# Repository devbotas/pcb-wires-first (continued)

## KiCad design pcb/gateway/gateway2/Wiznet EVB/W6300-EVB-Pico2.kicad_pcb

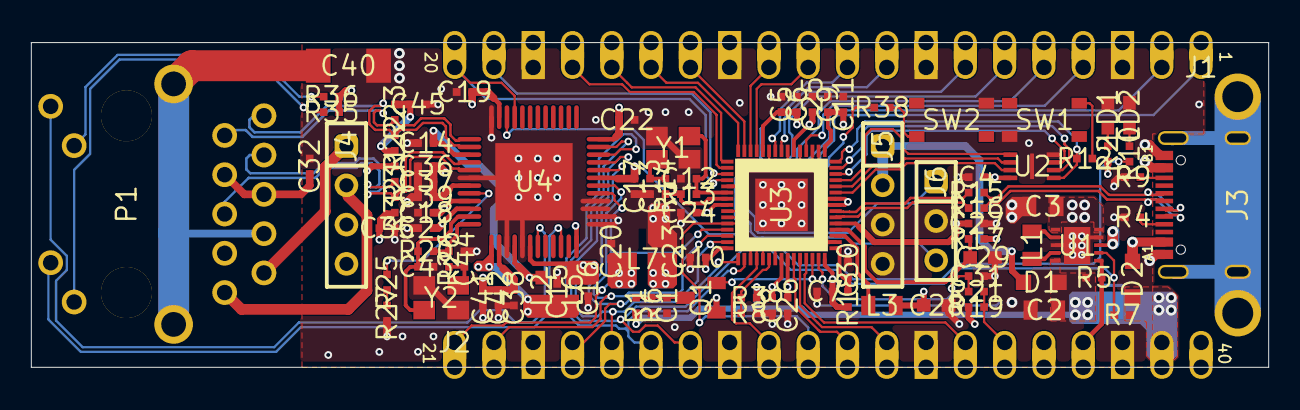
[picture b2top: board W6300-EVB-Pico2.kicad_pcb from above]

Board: 4 copper layers, 80.0 x 21.0 mm, 98 parts (0 on the bottom side), 89 nets.

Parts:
C1, C4, C6, C7, C8, C9, C10, C11, C14, C16, C17, C18, C19, C21, C22, C25, C26, C27, C32, C35, C36, C37, C39, C41, C42, C45: 0.1uF; CAP-0402
C2: 10u; CAP-0805
C3: 47u; CAP-0805
C5, C15, C20, C23, C24, C38: 1uF; CAP-0402
C12, C13: 15pF; CAP-0402
C28, C29: 10uF/1608; CAP-0603
C30, C31: 2u2; CAP-0402
C40: 1nF/2kV; CAP-1808
C43, C44: 18pF; CAP-0402
D1, D2: BAT60A; SOD-323(1-C,2-A)
J1, J2: 2.54mm 1x20 Pin Header DIP; IDC-1X20
J3: *; USB-TYPE-C-31-M-12
J4, J5: Header Socket 1x4_2.54mm; IDC-1X4(SOCKET)
J6: 2.54mm 1x3 Pin Header DIP; IDC-1X3
L1, L3: 2u2; IND-0805
L2, L6, L7: HH-1M1608-121JT; IND-0603
LD1: Green; LED-0603-RED
LD2: Green; LED-0603-GREEN
P1: TRJ4284AHNL; RB1-ZZ-0049
Q1: Q-2N7002; SOT23-3L
R1: 200K; RES-0402
R2, R10: 470R; RES-0402
R3: 5.6K; RES-0402
R4, R9: 5.1k; RES-0402
R5, R6, R7: 100K; RES-0402
R8: 10K; RES-0402
R12, R14, R38: 1K; RES-0402
R13: NC; RES-0402
R15, R16: 27R; RES-0402
R17, R26: 0R; RES-0402
R18: 10R; RES-0402
R19: 200R; RES-0402
R20: 1M; RES-0402
R21: 1R; RES-0402
R22, R23, R31, R32: 49.9R; RES-0402
R25: 12K/1%; RES-0402
R27: 300R; RES-0402
R35, R36: 330R; RES-0402
SW1, SW2: RKB2SJK250SMTR LFS; SW-RKB2
U1: SGM62112-3.3; SGM62112
U2: W25Q16JVUXIQ; SON50P300X200X60-9N
U3: RP2350-A; 7X7)
U4: W6300
Y1: 12MHz; OSC-TZ1067B
Y2: 25MHz; OSC-82J0626

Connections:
1V2A: C14.2, L2.1, U4.3, U4.16
1V2D: C16.2, C17.2, C18.2, C19.2, L6.2, U4.9, U4.18, U4.31, U4.47
1V2O: C15.2, L2.2, L6.1, U4.13
3V3: C3.2, C4.2, C5.2, C6.2, C7.2, C8.2, C9.2, C10.2, C11.2, C20.2, C21.2, C22.2, J2.16, L7.1, Q1.1, R2.1, R17.1, R18.1, R19.1, R35.2, R36.2, U1.1, U1.10, U2.8, U3.1, U3.11, U3.20, U3.30, U3.38, U3.45, U3.53, U3.54, U4.10, U4.24, U4.36
3V3A: C23.2, C32.2, C36.2, C37.2, C38.2, C39.2, C41.2, C42.2, L7.2, P1.R4, P1.R5, U4.7, U4.14
3V3_EN: J2.17, R5.2, U1.6
ACTn: P1.L2, U4.22
ADC_VREF: J2.15, R19.2, R21.2
CGND: C40.1, J3.S1, J3.S2, J3.S3, J3.S4, P1.R7, P1.S1, P1.S2
GPIO0: J1.1, U3.2
GPIO1: J1.2, U3.3
GPIO2: J1.4, U3.4
GPIO3: J1.5, U3.5
GPIO4: J1.6, U3.7
GPIO5: J1.7, U3.8
GPIO6: J1.9, U3.9
GPIO7: J1.10, U3.10
GPIO8: J1.11, U3.12
GPIO9: J1.12, U3.13
GPIO10: J1.14, U3.14
GPIO11: J1.15, U3.15
GPIO12: J1.16, U3.16
GPIO13: J1.17, U3.17
GPIO14: J1.19, U3.18
GPIO15: J1.20, U3.19, U4.45
GPIO16: J2.1, U3.27, U4.29
GPIO17: J2.2, U3.28, U4.30
GPIO18: J2.4, U3.29, U4.32
GPIO19: J2.5, U3.31, U4.33
GPIO20: J2.6, U3.32, U4.34
GPIO21: J2.7, U3.33, U4.35
GPIO22: J2.9, U3.34, U4.46
GPIO23: R7.2, U1.7, U3.35
GPIO24: R3.1, R8.2, U3.36
GPIO25: R10.2, U3.37
GPIO26/ADC0: J2.11, U3.40
GPIO27/ADC1: J2.12, U3.41
GPIO28/ADC2: J2.14, U3.42
GPIO29/ADC3: Q1.2, U3.43
LINKn: P1.L4, U4.19
NetC1_1: C1.1, Q1.3, R1.1, R6.2
NetC13_1: C13.1, R14.1, Y1.3
NetC31_2: C31.2, R21.1, U3.44
NetC35_2: C35.2, R31.1, R32.1
NetC43_2: C43.2, R20.1, U4.11, Y2.1
NetC44_2: C44.2, R26.1, Y2.3
NetC45_1: C45.1, R22.2, R23.2
NetJ3_A5: J3.A5, R4.1
NetJ3_B5: J3.B5, R9.2
NetL1_1: L1.1, U1.4
NetL1_2: L1.2, U1.2
NetLD1_1: LD1.1, R2.2
NetLD2_1: LD2.1, R10.1
NetP1_L1: P1.L1, R35.1
NetP1_L3: P1.L3, R36.1
NetP1_R1: P1.R1, R22.1, U4.2
NetP1_R2: P1.R2, R23.1, U4.1
NetP1_R3: P1.R3, R32.2, U4.5
NetP1_R6: P1.R6, R31.2, U4.4
NetR12_2: R12.2, SW1.2
NetR15_1: R15.1, U3.52
NetR16_1: R16.1, U3.51
NetR20_2: R20.2, R26.2, U4.12
NetR25_1: R25.1, U4.8
NetR25_2: R25.2, R27.1
NetR38_1: R38.1, SW2.2
POE: D1.2, J5.1, J5.2
QSPI_SCLK: U2.6, U3.56
QSPI_SD0: U2.5, U3.57
QSPI_SD1: U2.2, U3.59
QSPI_SD2: U2.3, U3.58
QSPI_SD3: U2.7, U3.55
QSPI_SS: R12.1, U2.1, U3.60
RUN: J2.10, R38.2, U3.26
SWCLK: J6.1, U3.24
SWDIO: J6.3, U3.25
USB_DM: J3.A7, J3.B7, R16.2
USB_DP: J3.A6, J3.B6, R15.2
VBUS: D2.2, J2.20, J3.A4_B9, J3.B4_A9
VC1: J4.1, P1.R9
VC2: J4.2, P1.R10
VREG_AVDD: C30.2, R18.2, U3.46
VREG_FB: C24.2, C25.2, C26.2, C27.2, C28.2, L3.2, U3.6, U3.23, U3.39, U3.50
VREG_LX: L3.1, U3.48
VREG_PGND: C1.2, C2.1, C3.1, C4.1, C5.1, C6.1, C7.1, C8.1, C9.1, C10.1, C11.1, C12.2, C13.2, C14.1, C15.1, C16.1, C17.1, C18.1, C19.1, C20.1, C21.1, C22.1, C23.1, C24.1, C25.1, C26.1, C27.1, C28.1, C29.1, C30.1, C31.1, C32.1, C35.1, C36.1, C37.1, C38.1, C39.1, C40.2, C41.1, C42.1, C43.1, C44.1, C45.2, J1.3, J1.8, J1.13, J1.18, J2.3, J2.8, J2.13, J2.18, J3.A1_B12, J3.B1_A12, J5.3, J5.4, J6.2, LD1.2, LD2.2, R4.2, R6.1, R8.1, R9.1, R27.2, SW1.3, SW2.3, U1.3, U1.9, U2.4, U2.9, U3.47, U3.61, U4.6, U4.15, U4.17, U4.25, U4.26, U4.27, U4.28, U4.48, U4.49, Y1.2, Y1.4, Y2.2, Y2.4
VREG_VIN: C29.2, R17.2, U3.49
VSYS: C2.2, D1.1, D2.1, J2.19, R1.2, R3.2, R5.1, R7.1, U1.5, U1.8
XIN: C12.1, R13.2, U3.21, Y1.1
XOUT: R13.1, R14.2, U3.22

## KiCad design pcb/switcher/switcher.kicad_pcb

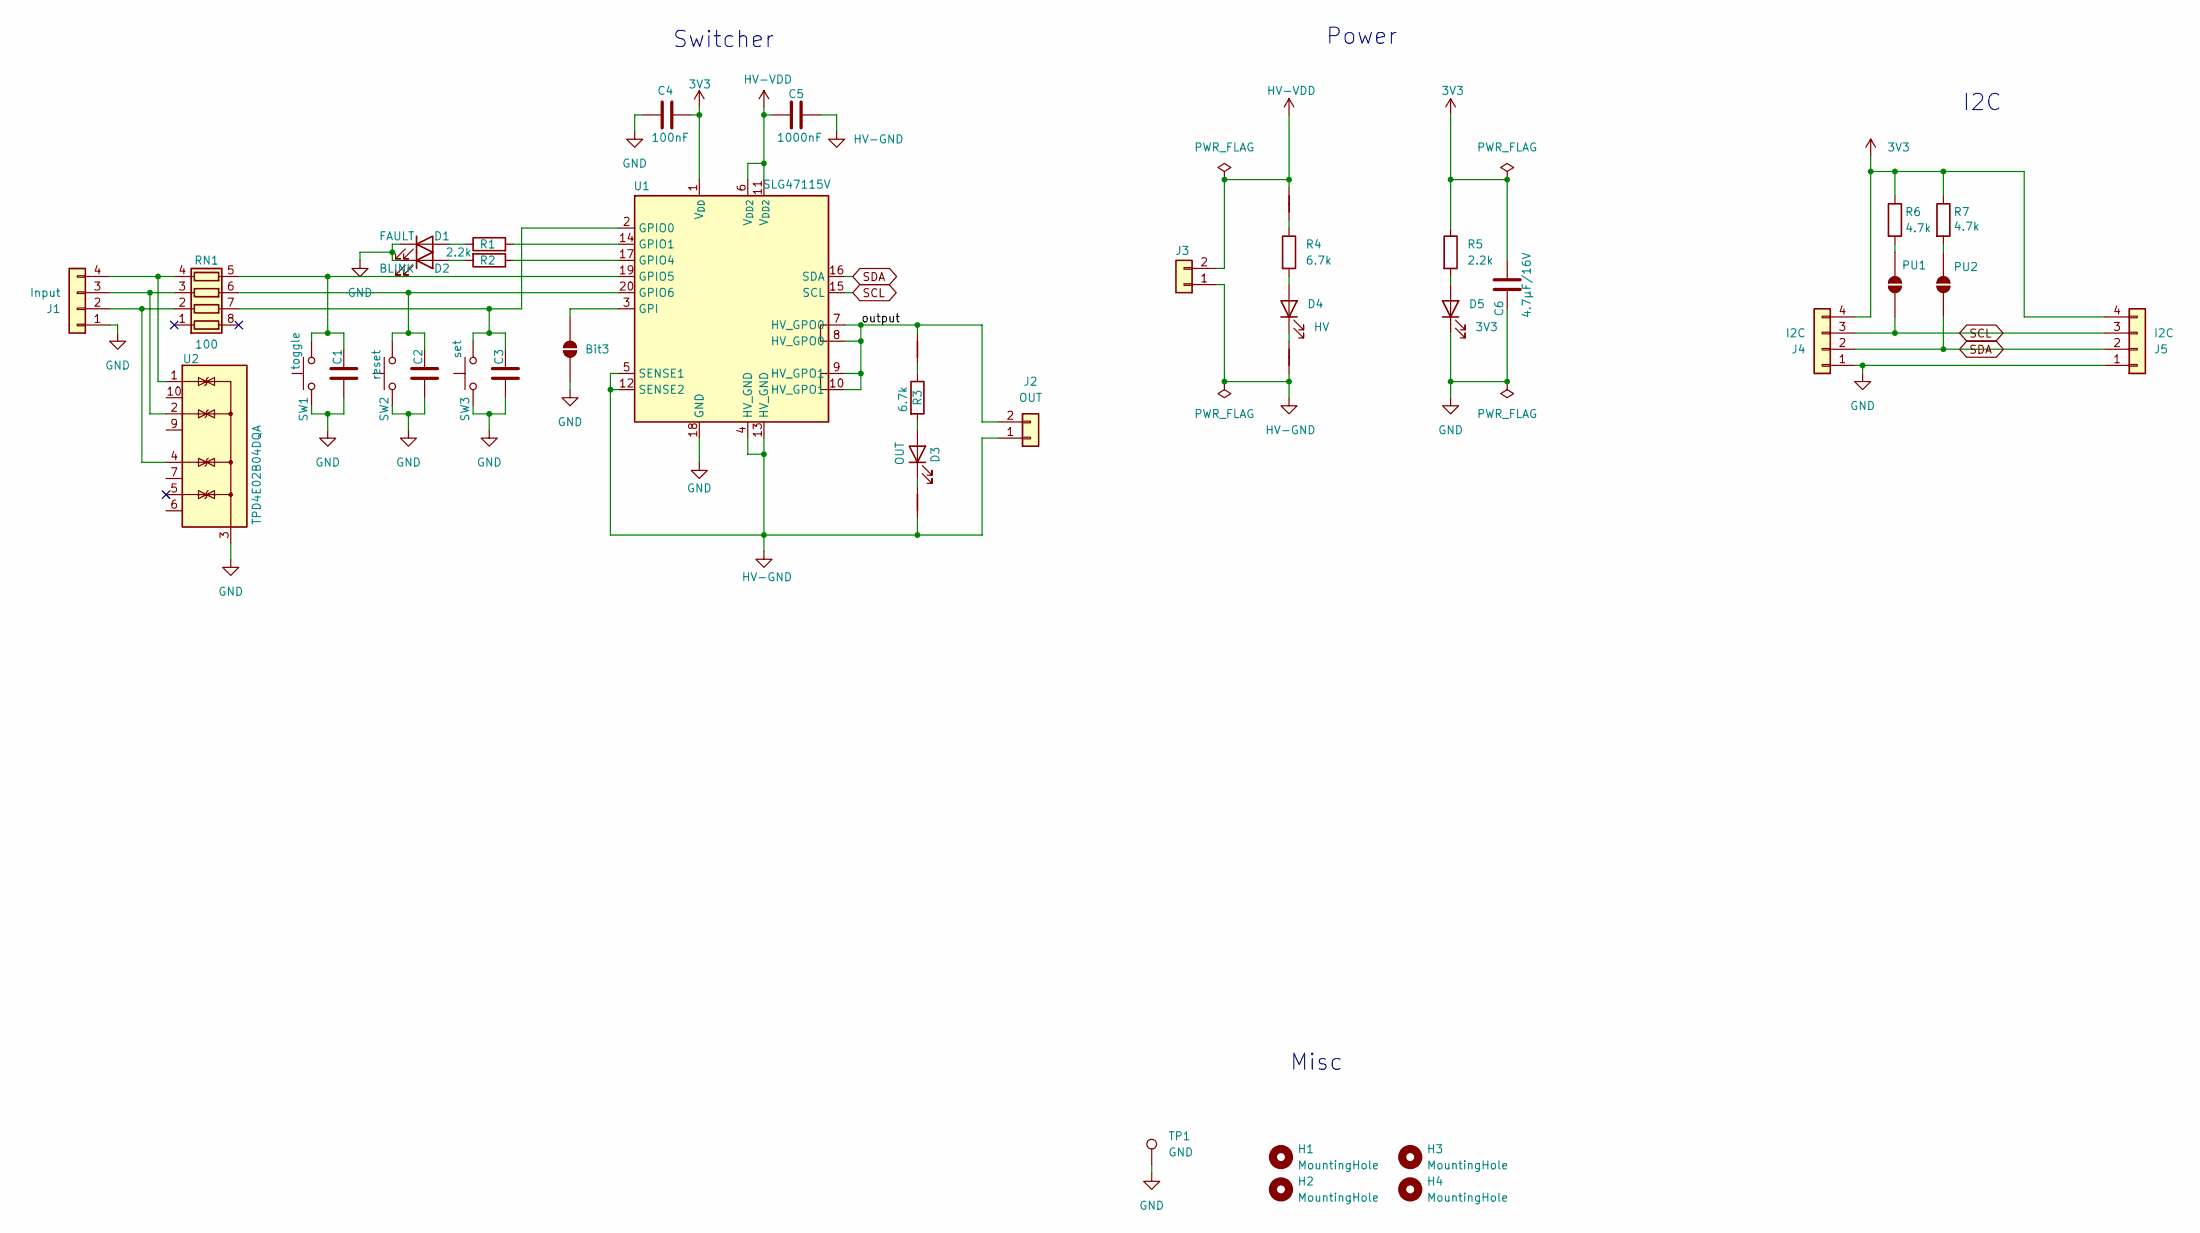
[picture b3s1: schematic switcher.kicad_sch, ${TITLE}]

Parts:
Bit3: SolderJumper_2_Open; SolderJumper-2_P1.3mm_Open_RoundedPad1.0x1.5mm
C1, C2, C3, C4: 100nF; C_0603_1608Metric
C5: 1000nF; C_0603_1608Metric
C6: 4.7μF/16V; C_0603_1608Metric
D1: FAULT; D_0603_1608Metric
D2: BLINK; D_0603_1608Metric
D3: OUT; D_0603_1608Metric
D4: HV; D_0603_1608Metric
D5: 3V3; D_0603_1608Metric
H1, H2, H3, H4: MountingHole; MountingHole_3.2mm_M3_NoCopper
J1: Input; PhoenixContact_MCV_1,5_4-G-3.5_1x04_P3.50mm_Vertical
J2: OUT; JST_VH_B2P-VH_1x02_P3.96mm_Vertical
J3: Conn_01x02; JST_VH_B2P-VH_1x02_P3.96mm_Vertical
J4, J5: I2C; JST_XH_B4B-XH-A_1x04_P2.50mm_Vertical
NT1, NT3, NT4: NetTie_2; NetTie-2_SMD_Pad0.5mm
NT2: NetTie_2; NetTie-2_THT_Pad0.3mm
PU1, PU2: SolderJumper_2_Open; SolderJumper-2_P1.3mm_Open_RoundedPad1.0x1.5mm
R1, R2, R5: 2.2k; R_0603_1608Metric
R3, R4: 6.7k; R_0603_1608Metric
R6, R7: 4.7k; R_0603_1608Metric
RN1: 100; R_Array_Concave_4x0603
SW1: toggle; SW_SPST_B3U-1000P
SW2: reset; SW_SPST_B3U-1000P
SW3: set; SW_SPST_B3U-1000P
TP1: GND; TestPoint_Keystone_5019_Miniature
U1: SLG47115V; Renesas_UQFN-20_2x3mm_P0.4mm_SLG47115V
U2: TPD4E02B04DQA; USON-10_2.5x1.0mm_P0.5mm

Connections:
3V3: C4.2, C6.1, J4.4, J5.4, R5.1, R6.1, R7.1, U1.1 (V_{DD})
/output: J2.2, NT1.2, U1.7 (HV_GPO0), U1.8 (HV_GPO0), U1.9 (HV_GPO1), U1.10 (HV_GPO1)
GND: Bit3.1 (A), C1.1, C2.1, C3.1, C4.1, C6.2, D1.1 (K), D2.1 (K), D5.1 (K), J1.1, J4.1, J5.1, SW1.1, SW2.1, SW3.1, TP1.1 (1_1), U1.18 (GND), U2.3 (G), U2.8 (G)
HV-GND: C5.1, J2.1, J3.1, NT2.1, NT4.1, U1.4 (HV_GND), U1.5 (SENSE1), U1.12 (SENSE2), U1.13 (HV_GND)
HV-VDD: C5.2, J3.2, NT3.2, U1.6 (V_{DD2}), U1.11 (V_{DD2})
unnamed: Bit3.2 (B), U1.3 (GPI)
unnamed: D1.2 (A), R1.1
unnamed: D2.2 (A), R2.2
unnamed: D3.2 (A), R3.2
unnamed: D3.1 (K), NT2.2
unnamed: D4.2 (A), R4.2
unnamed: D4.1 (K), NT4.2
unnamed: D5.2 (A), R5.2
unnamed: J1.2, RN1.2 (R2.1), U2.4 (IO3)
unnamed: J1.3, RN1.3 (R3.1), U2.2 (IO2)
unnamed: J1.4, RN1.4 (R4.1), U2.1 (IO1)
unnamed: NT1.1, R3.1
unnamed: NT3.1, R4.1
unnamed: PU1.2 (B), R6.2
unnamed: PU2.2 (B), R7.2
unnamed: C3.2, RN1.7 (R2.2), SW3.2, U1.2 (GPIO0)
unnamed: C2.2, RN1.6 (R3.2), SW2.2, U1.20 (GPIO6)
unnamed: C1.2, RN1.5 (R4.2), SW1.2, U1.19 (GPIO5)
unnamed: R1.2, U1.14 (GPIO1)
unnamed: R2.1, U1.17 (GPIO4)
SCL: J4.3, J5.3, PU1.1 (A), U1.15 (SCL)
SDA: J4.2, J5.2, PU2.1 (A), U1.16 (SDA)

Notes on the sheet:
Switcher
I2C
Power
Misc

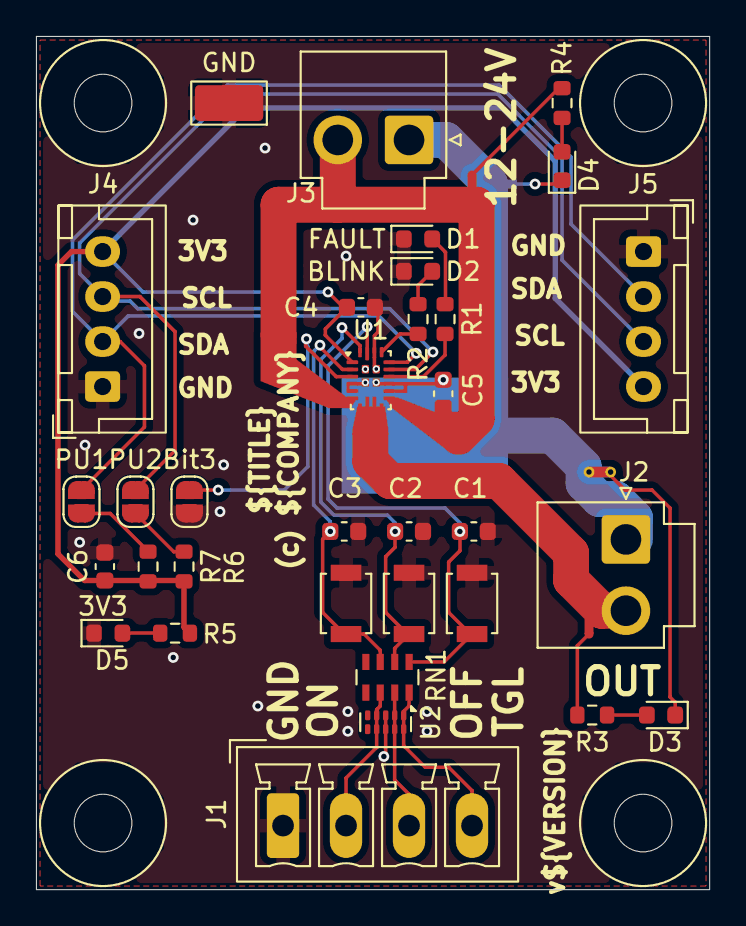
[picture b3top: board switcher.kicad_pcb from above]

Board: 2 copper layers, 37.4 x 47.4 mm, 41 parts (1 on the bottom side), 27 nets.

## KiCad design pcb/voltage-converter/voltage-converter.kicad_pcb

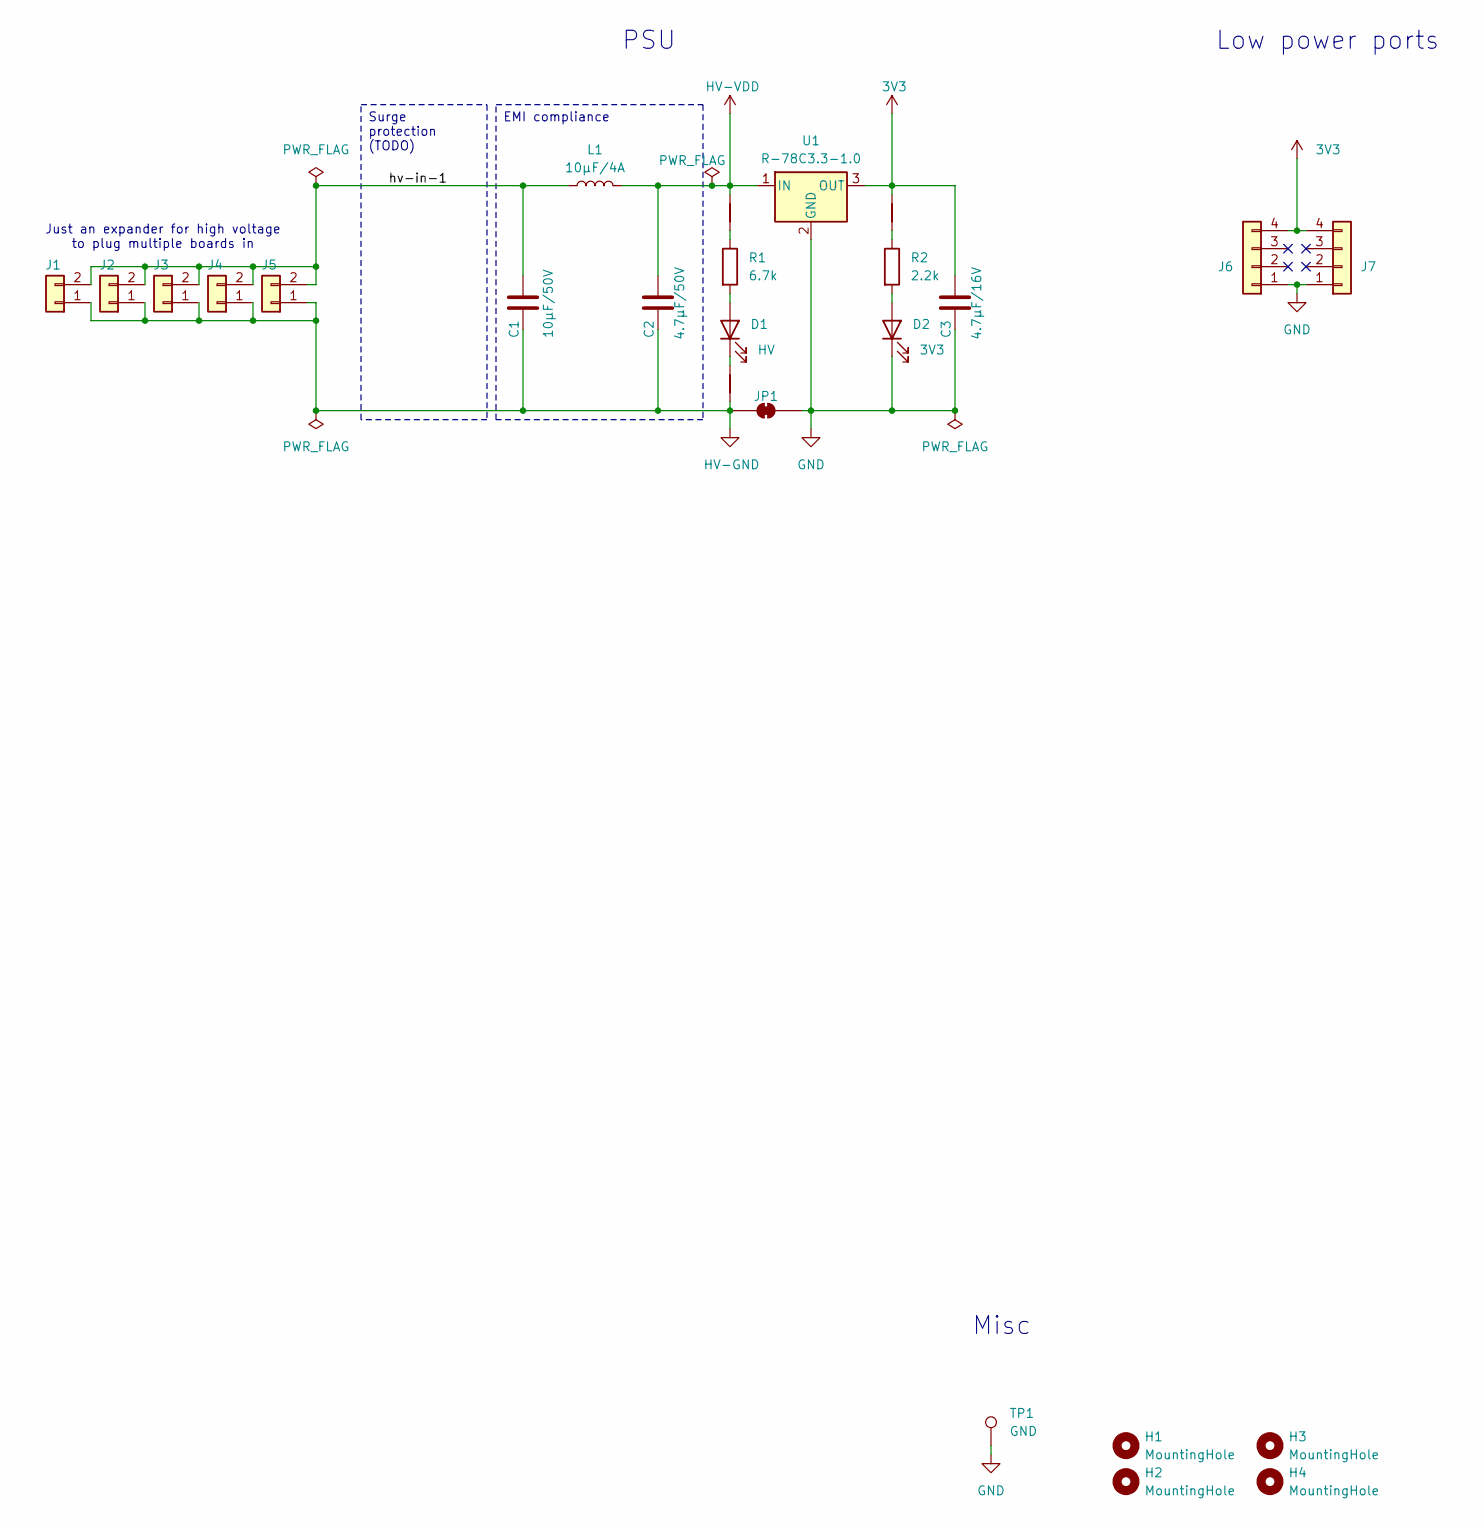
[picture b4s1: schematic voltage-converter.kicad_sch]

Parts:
C1: 10μF/50V; C_1206_3216Metric
C2: 4.7μF/50V; C_1206_3216Metric
C3: 4.7μF/16V; C_0603_1608Metric
D1: HV; D_0603_1608Metric
D2: 3V3; D_0603_1608Metric
H1, H2, H3, H4: MountingHole; MountingHole_3.2mm_M3_NoCopper
J1, J2, J3, J4, J5: Conn_01x02; JST_VH_B2P-VH_1x02_P3.96mm_Vertical
J6, J7: JST_XH_B4B-XH-A_1x04_P2.50mm_Vertical
JP1: SolderJumper_2_Bridged; SolderJumper-2_P1.3mm_Bridged_RoundedPad1.0x1.5mm
L1: 10μF/4A; L_Bourns_SRP7028A_7.3x6.6mm
NT1, NT2, NT3: NetTie_2; NetTie-2_SMD_Pad0.5mm
R1: 6.7k; R_0603_1608Metric
R2: 2.2k; R_0603_1608Metric
TP1: GND; TestPoint_Keystone_5019_Miniature
U1: R-78C3.3-1.0; Converter_DCDC_RECOM_R-78E-0.5_THT

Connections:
3V3: C3.1, J6.4, J7.4, NT3.2, U1.3 (OUT)
/hv-in-1: C1.1, J1.2, J2.2, J3.2, J4.2, J5.2, L1.1
GND: C3.2, D2.1 (K), J6.1, J7.1, JP1.2 (B), TP1.1 (1_1), U1.2 (GND)
HV-GND: C1.2, C2.2, J1.1, J2.1, J3.1, J4.1, J5.1, JP1.1 (A), NT2.1
HV-VDD: C2.1, L1.2, NT1.2, U1.1 (IN)
unnamed: D1.2 (A), R1.2
unnamed: D1.1 (K), NT2.2
unnamed: D2.2 (A), R2.2
unnamed: NT1.1, R1.1
unnamed: NT3.1, R2.1

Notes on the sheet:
Just an expander for high voltage to plug multiple boards in
Low power ports
PSU
Misc
Surge protection (TODO)
EMI compliance

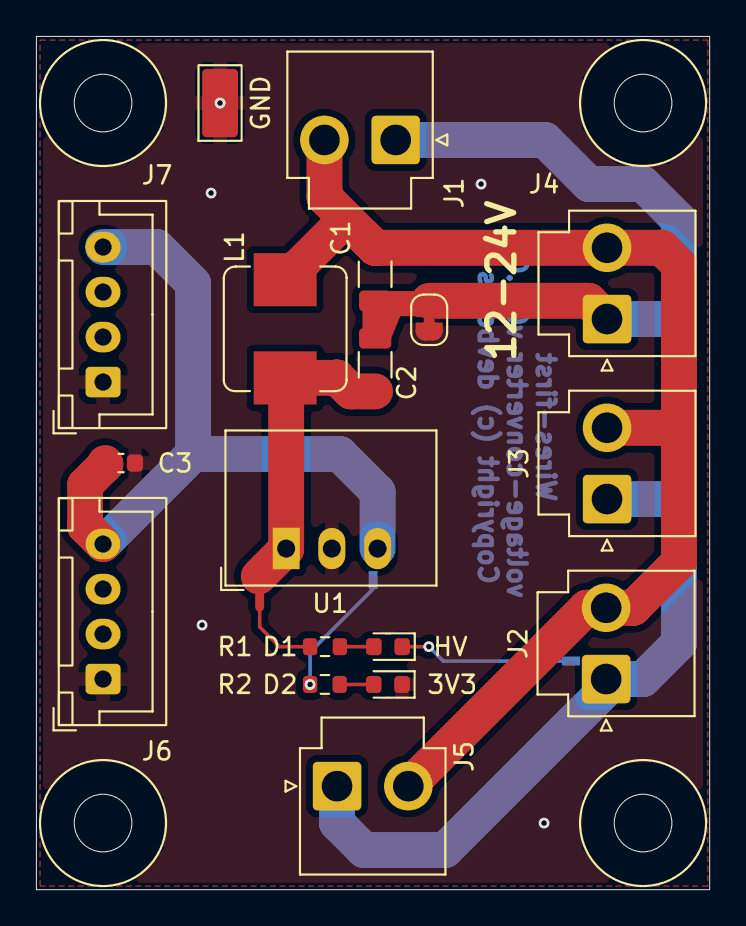
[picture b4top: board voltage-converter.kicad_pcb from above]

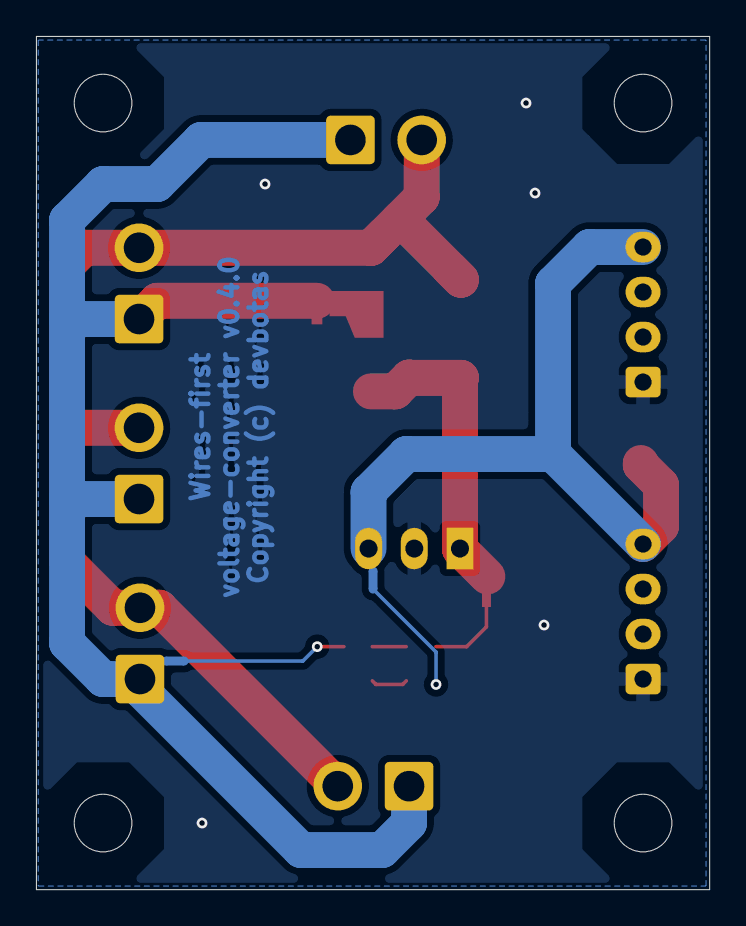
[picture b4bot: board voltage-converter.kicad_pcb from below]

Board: 2 copper layers, 37.4 x 47.4 mm, 25 parts (2 on the bottom side), 10 nets.

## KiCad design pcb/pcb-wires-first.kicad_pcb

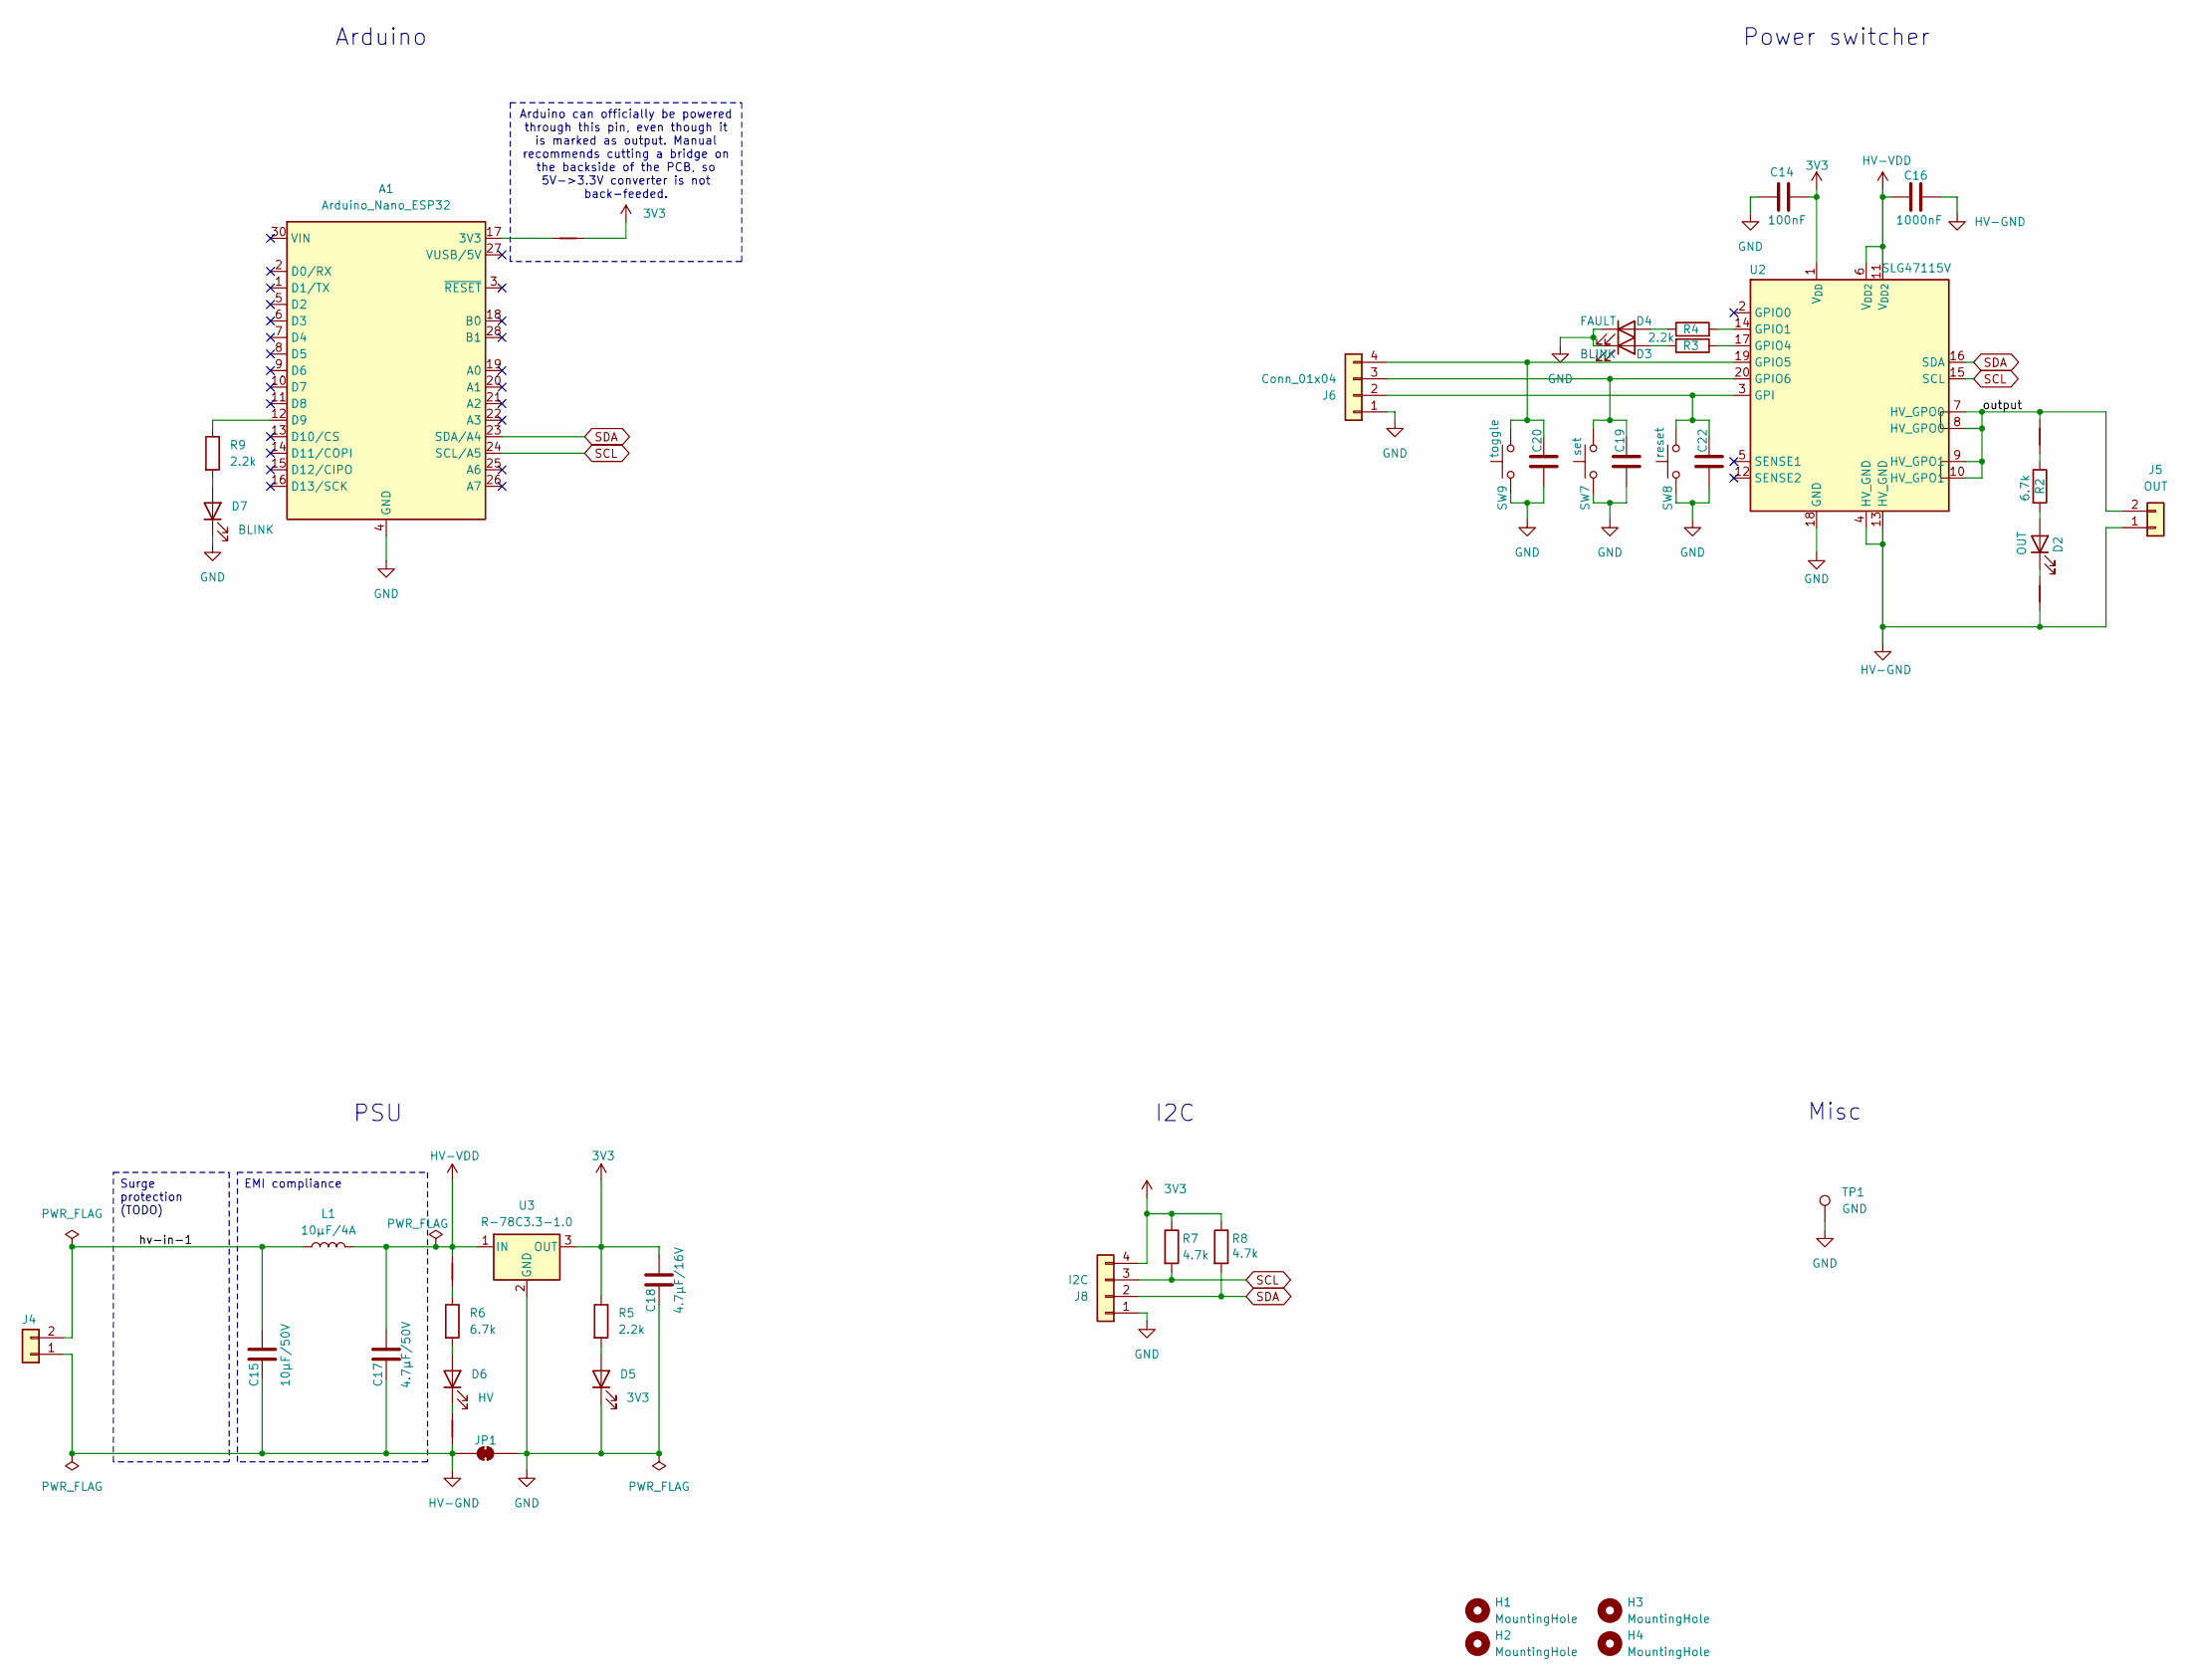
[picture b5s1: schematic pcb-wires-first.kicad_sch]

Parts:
A1: Arduino_Nano_ESP32; Arduino_Nano
C14, C19, C20, C22: 100nF; C_0603_1608Metric
C15: 10μF/50V; C_1206_3216Metric
C16: 1000nF; C_0603_1608Metric
C17: 4.7μF/50V; C_1206_3216Metric
C18: 4.7μF/16V; C_0603_1608Metric
D2: OUT; D_0603_1608Metric
D3, D7: BLINK; D_0603_1608Metric
D4: FAULT; D_0603_1608Metric
D5: 3V3; D_0603_1608Metric
D6: HV; D_0603_1608Metric
H1, H2, H3, H4: MountingHole; MountingHole_3.2mm_M3_NoCopper
J4: Conn_01x02; JST_VH_B2P-VH_1x02_P3.96mm_Vertical
J5: OUT; JST_VH_B2P-VH_1x02_P3.96mm_Vertical
J6: Conn_01x04; PhoenixContact_MCV_1,5_4-G-3.5_1x04_P3.50mm_Vertical
J8: I2C; JST_XH_B4B-XH-A_1x04_P2.50mm_Vertical
JP1: SolderJumper_2_Bridged; SolderJumper-2_P1.3mm_Bridged_RoundedPad1.0x1.5mm
L1: 10μF/4A; L_Bourns_SRP7028A_7.3x6.6mm
NT1, NT2, NT3, NT4: NetTie_2; NetTie-2_SMD_Pad0.5mm
NT5: NetTie_2; NetTie-2_THT_Pad0.3mm
R2, R6: 6.7k; R_0603_1608Metric
R3, R4, R5, R9: 2.2k; R_0603_1608Metric
R7, R8: 4.7k; R_0603_1608Metric
SW7: set; SW_SPST_B3U-1000P
SW8: reset; SW_SPST_B3U-1000P
SW9: toggle; SW_SPST_B3U-1000P
TP1: GND; TestPoint_Keystone_5019_Miniature
U2: SLG47115V; Renesas_UQFN-20_2x3mm_P0.4mm_LayoutBorder4x6y
U3: R-78C3.3-1.0; Converter_DCDC_RECOM_R-78E-0.5_THT

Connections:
3V3: C14.2, C18.1, J8.4, NT1.2, R5.1, R7.1, R8.1, U2.1 (V_{DD}), U3.3 (OUT)
/hv-in-1: C15.1, J4.2, L1.1
/output: J5.2, NT4.2, U2.7 (HV_GPO0), U2.8 (HV_GPO0), U2.9 (HV_GPO1), U2.10 (HV_GPO1)
GND: A1.4 (GND), A1.29 (GND), C14.1, C18.2, C19.1, C20.1, C22.1, D3.1 (K), D4.1 (K), D5.1 (K), D7.1 (K), J6.1, J8.1, JP1.2 (B), SW7.1, SW8.1, SW9.1, TP1.1 (1_1), U2.18 (GND), U3.2 (GND)
HV-GND: C15.2, C16.1, C17.2, J4.1, J5.1, JP1.1 (A), NT3.1, NT5.1, U2.4 (HV_GND), U2.13 (HV_GND)
HV-VDD: C16.2, C17.1, L1.2, NT2.2, U2.6 (V_{DD2}), U2.11 (V_{DD2}), U3.1 (IN)
unnamed: A1.17 (3V3), NT1.1
unnamed: A1.12 (D9), R9.1
unnamed: D2.2 (A), R2.2
unnamed: D2.1 (K), NT5.2
unnamed: D3.2 (A), R3.2
unnamed: D4.2 (A), R4.1
unnamed: D5.2 (A), R5.2
unnamed: D6.2 (A), R6.2
unnamed: D6.1 (K), NT3.2
unnamed: D7.2 (A), R9.2
unnamed: C22.2, J6.2, SW8.2, U2.3 (GPI)
unnamed: C19.2, J6.3, SW7.2, U2.20 (GPIO6)
unnamed: C20.2, J6.4, SW9.2, U2.19 (GPIO5)
unnamed: NT2.1, R6.1
unnamed: NT4.1, R2.1
unnamed: R4.2, U2.14 (GPIO1)
unnamed: R3.1, U2.17 (GPIO4)
SCL: A1.24 (SCL/A5), J8.3, R7.2, U2.15 (SCL)
SDA: A1.23 (SDA/A4), J8.2, R8.2, U2.16 (SDA)

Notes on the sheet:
Power switcher
I2C
PSU
Misc
Arduino
Arduino can officially be powered through this pin, even though it is marked as output. Manual recommends cutting a bridge on the backside of the PCB, so 5V->3.3V converter is not back-feeded.
Surge protection (TODO)
EMI compliance

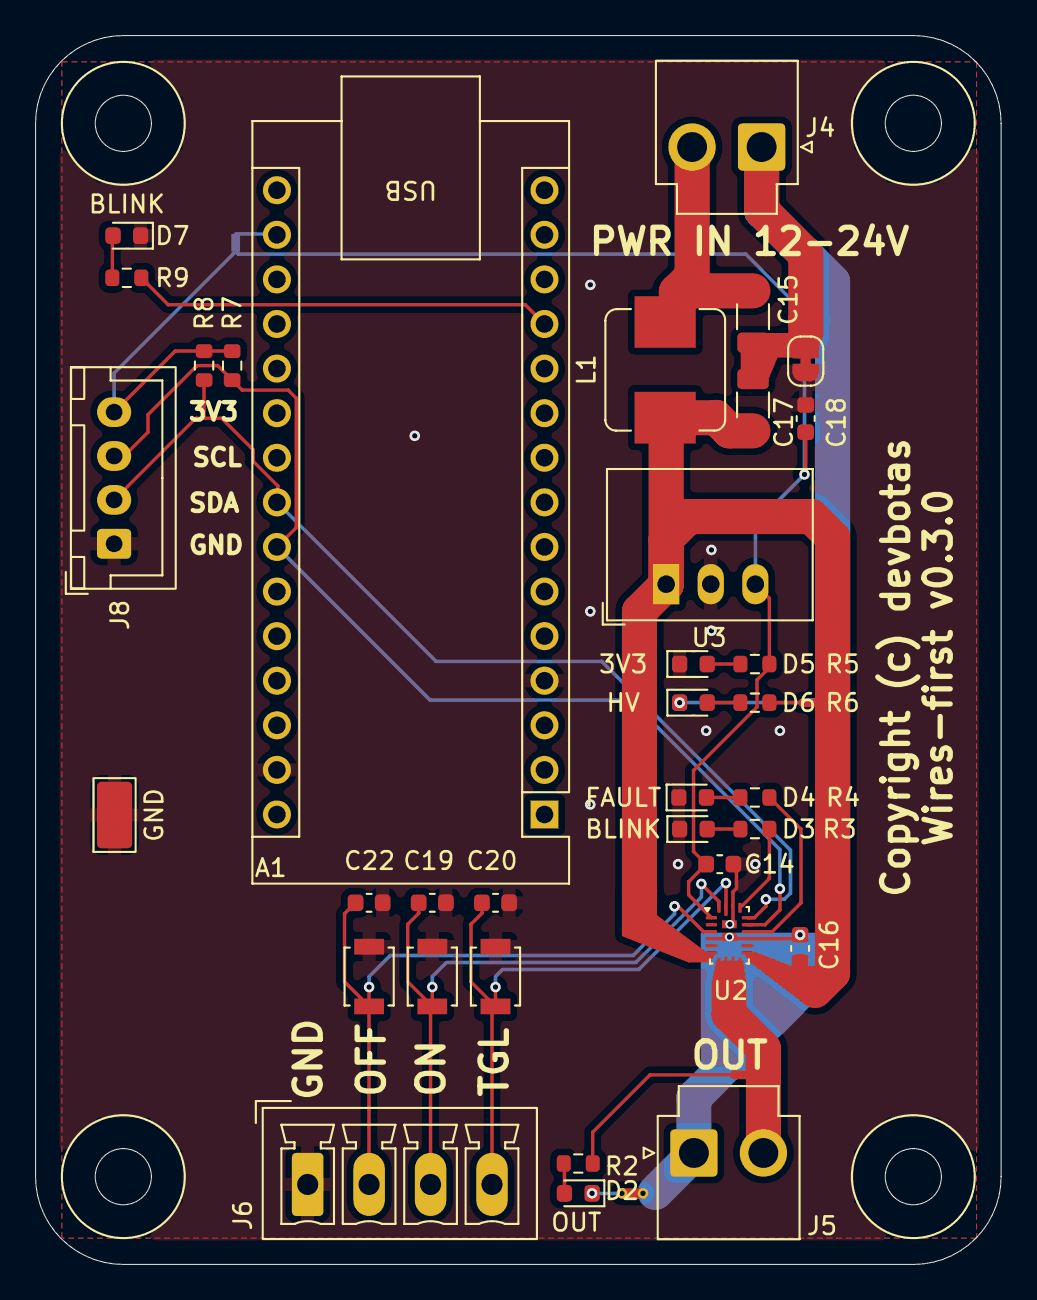
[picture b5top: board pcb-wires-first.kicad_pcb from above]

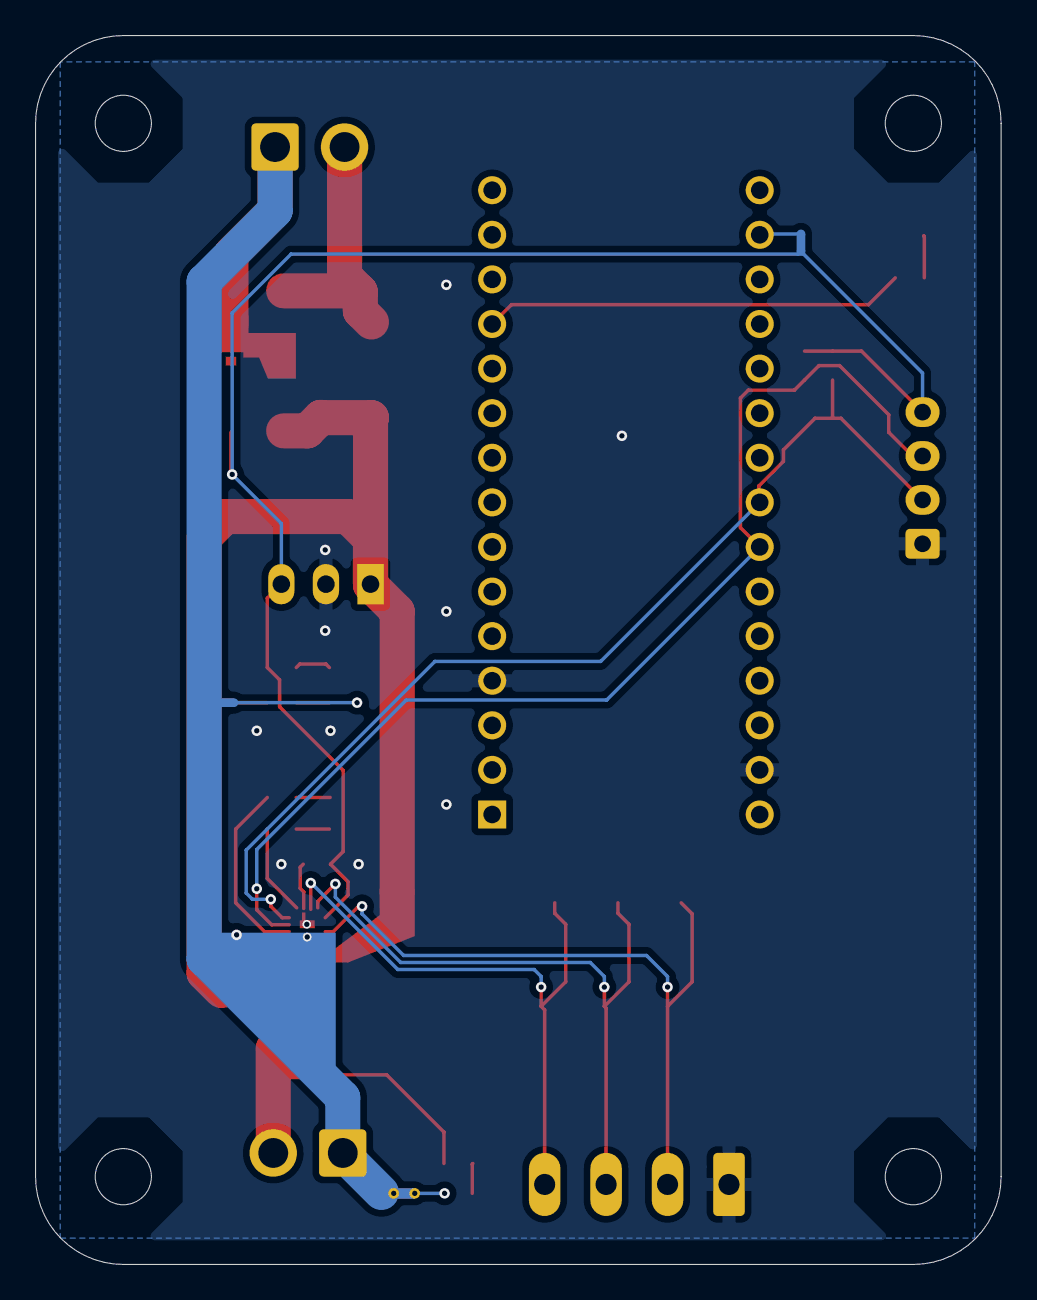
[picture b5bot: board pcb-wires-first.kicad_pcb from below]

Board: 2 copper layers, 55.0 x 70.0 mm, 44 parts (2 on the bottom side), 25 nets.

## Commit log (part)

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2026-04-30 Creating a SLG47115 symbol.
2026-04-30 Drafting.
2026-05-04 Adding SLG47105, SLG47115 and SLG46826 symbols.
2026-05-04 Drafting the board.
2026-05-05 WIP.
2026-05-05 Working on PSU part mostly.
2026-05-05 Getting rid of the warnings.
2026-05-05 Tidying up schematic.
2026-05-06 Routing the board.
2026-05-06 Manually overriding clearance of some of those QFN pads. They are too close. Footprint bug.
2026-05-06 More routing.
2026-05-06 Routed!
2026-05-11 Adding an I2C connector.
2026-05-11 Doing a draft release.
2026-05-19 Adding some readme.
2026-05-19 Repouring?..
2026-06-03 Adding a custom mounting hole footprint which excludes copper.
2026-06-03 Adding more testpoints.
2026-06-03 Some SLG footprint pads have exclusions zones quasi-overlap by 0.00001, so disabling these DRC violations.
2026-06-03 Vibe coding 3D model copyier to stock libraries app into existence.
2026-06-03 Fixing the vibe-coded app (manually).
2026-06-03 Temporary commiting the app execs.
2026-06-04 Moving model pusher into a separate project.
2026-06-04 Adjusting tracks.
2026-06-05 Adding notes for vNext.
2026-06-08 Completely reworking the entire thing. It is sinble-channel now.
2026-06-09 IO6 and IO7 are GPO on 46826
2026-06-09 Adding blinker for Arduino.
2026-06-09 Cleaning up DRC violations in PCB.
2026-06-09 Some more cleanup.
2026-06-09 Updating readme.
2026-06-10 Some fine tuning.
2026-06-10 Moar fine-tuning.
2026-06-24 Updating to new libs.
2026-06-24 Updating PCB.
